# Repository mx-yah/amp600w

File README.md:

# High-efficiency 600W sound amplifier

A high-performance high-power class-D amplifier that enables true premium 
sound quality with high-efficiency class-D technology

Based on the TPA3255DDV integrated circuit from Texas Instruments.

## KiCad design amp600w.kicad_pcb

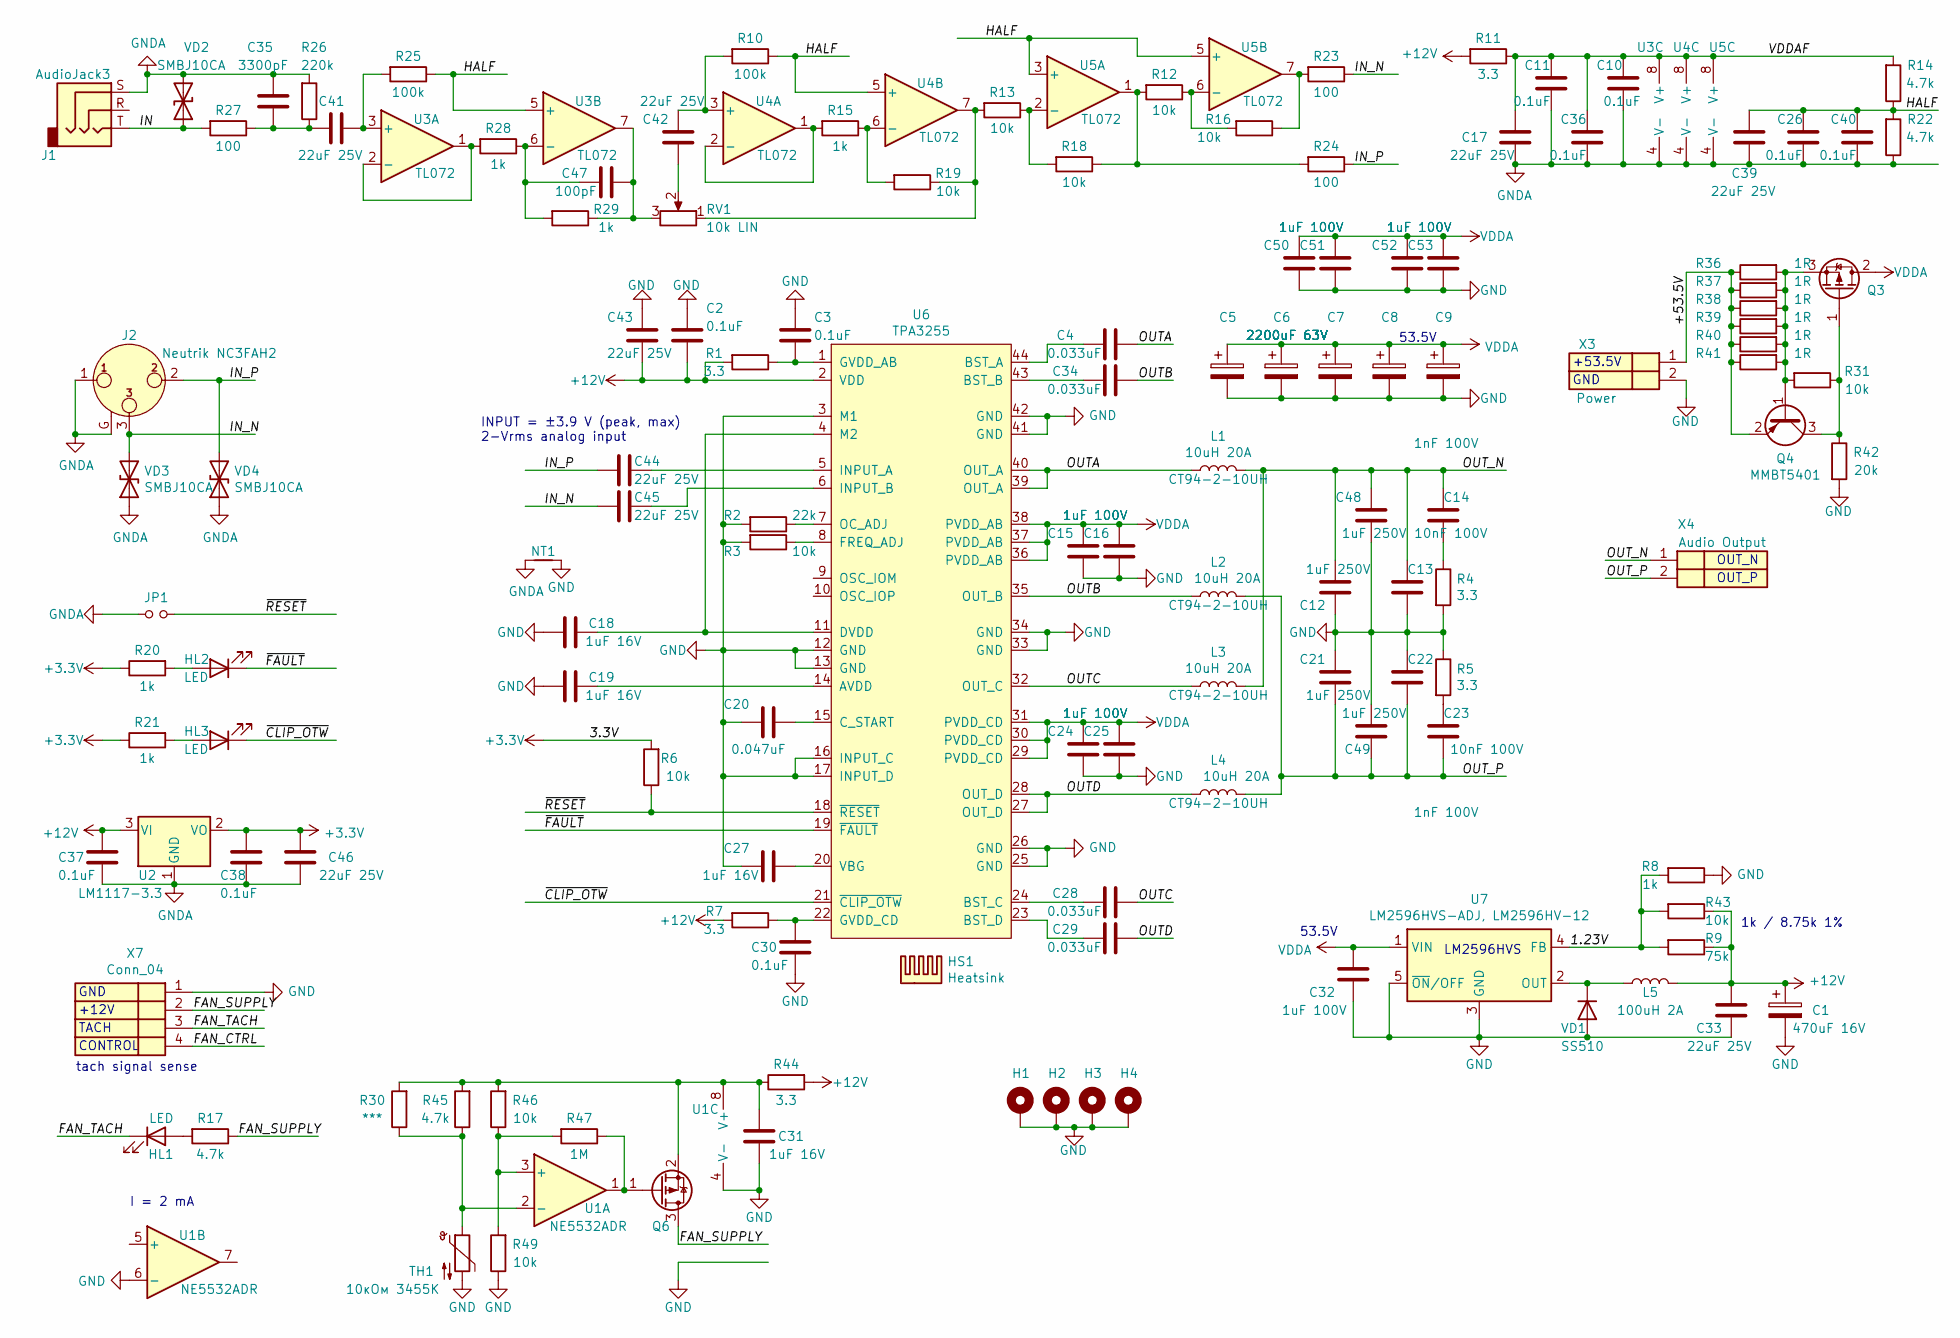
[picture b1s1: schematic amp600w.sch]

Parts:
C1: 470uF 16V; CP_Radial_D8.0mm_P3.50mm
C2, C3, C10, C11, C26, C30, C36, C37, C38, C40: 0.1uF; C_0603_1608Metric
C4, C28, C29, C34: 0.033uF; C_0603_1608Metric
C5, C6, C7, C8, C9: 2200uF 63V; CP_Radial_D18.0mm_P7.50mm
C12, C21, C48, C49: 1uF 250V; C_Rect_L18.0mm_W9.0mm_P15.00mm_FKS3_FKP3
C13, C22: 1nF 100V; C_1206_3216Metric
C14, C23: 10nF 100V; C_0805_2012Metric
C15, C16, C24, C25, C32, C50, C51, C52, C53: 1uF 100V; C_1210_3225Metric
C17, C33, C39, C41, C42, C43, C44, C45, C46: 22uF 25V; C_1210_3225Metric
C18, C19, C27, C31: 1uF 16V; C_0603_1608Metric
C20: 0.047uF; C_0603_1608Metric
C35: 3300pF; C_0603_1608Metric
C47: 100pF; C_0603_1608Metric
H1, H2, H3, H4: MountingHole_Pad; MountingHole_3.5mm_Pad_Via
HL1: LED; LED_D3.0mm
HL2, HL3: LED; LED_D3.0mm_Horizontal_O6.35mm_Z6.0mm
HS1: Heatsink; HEATSINK_LGA1156
J1: AudioJack3; Jack_3.5mm_Switronic_ST-005-G_horizontal
J2: XLR3_Ground; Jack_XLR_Neutrik_NC3FAH2_Horizontal
JP1: Jumper_NO_Small; PinHeader_1x02_P2.54mm_Vertical
L1, L2, L3, L4: 10uH 20A; L_Toroid_Vertical_L33.0mm_W17.8mm_P12.70mm_Pulse_KM-5
L5: 100uH 2A; L_12x12mm_H8mm
NT1: Net-Tie_2; NetTie-2_SMD_Pad0.5mm
Q3: IRF9540NSTRLPBF; TO-263-2
Q4: MMBT5401; SOT-23
Q6: IRLML9303; SOT-23
R1, R4, R5, R7, R11, R44: 3.3; R_1206_3216Metric
R2: 22k; R_0603_1608Metric
R3, R6, R12, R13, R16, R18, R19, R31, R43, R46, R49: 10k; R_0603_1608Metric
R8, R15, R20, R21, R28, R29: 1k; R_0603_1608Metric
R9: 75k; R_0603_1608Metric
R10, R25: 100k; R_0603_1608Metric
R14, R17, R22, R45: 4.7k; R_0603_1608Metric
R23, R24, R27: 100; R_0603_1608Metric
R26: 220k; R_0603_1608Metric
R30: ***; R_0603_1608Metric
R36, R37, R38, R39, R40, R41: 1R; R_1812_4532Metric
R42: 20k; R_0805_2012Metric
R47: 1M; R_0603_1608Metric
RV1: 10k LIN; Potentiometer_Piher_T-16H_Single_Horizontal
TH1: 10кОм 3455K; R_0603_1608Metric
U1: NE5532ADR; SO-8_3.9x4.9mm_P1.27mm
U2: LM1117-3.3; SOT-223-3_TabPin2
U3, U4, U5: TL072; SO-8_3.9x4.9mm_P1.27mm
U6: TPA3255; TPA3255DDV
U7: LM2596HVS-ADJ, LM2596HV-12; TO-263-5_TabPin3
VD1: SS510; D_SMC
VD2, VD3, VD4: SMBJ10CA; D_SMB
X3: Power; TerminalBlock_Degson_DG25C-B_P7.62mm
X4: Audio Output; TerminalBlock_Degson_DG25C-B_P7.62mm
X7: Conn_04; FanPinHeader_1x04_P2.54mm_Vertical

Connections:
+3V3: C38.2, C46.1, R6.2, R20.1, R21.1, U2.2 (VO)
+12V: C1.1, C2.2, C33.2, C37.2, C43.2, L5.2, R1.2, R7.2, R9.1, R11.2, R43.1, R44.2, U2.3 (VI), U6.2 (VDD)
/1.23V: R8.2, R9.2, R43.2, U7.4 (FB)
/+53.5V: Q4.2 (E), R36.1, R37.1, R38.1, R39.1, R40.1, R41.1, X3.1
/FAN_SUPPLY: Q6.3 (D), R17.1, X7.2
/FAN_TACH: HL1.1 (K), X7.3
/HALF: C26.2, C39.1, C40.1, R10.1, R14.1, R22.2, R25.1, U3.5 (+), U4.5 (+), U5.3 (+), U5.5 (+)
/IN: J1.T, R27.2, VD2.1 (A1)
/IN_N: C45.2, J2.3, R23.1, VD3.2 (A2)
/IN_P: C44.2, J2.2, R24.1, VD4.2 (A2)
/OUTA: C4.1, L1.1, U6.39 (OUT_A), U6.40 (OUT_A)
/OUTB: C34.1, L2.1, U6.35 (OUT_B)
/OUTC: C28.1, L3.1, U6.32 (OUT_C)
/OUTD: C29.1, L4.1, U6.27 (OUT_D), U6.28 (OUT_D)
/OUT_N: C12.2, C13.2, C14.2, C48.2, L1.2, L3.2, X4.1
/OUT_P: C21.1, C22.1, C23.1, C49.1, L2.2, L4.2, X4.2
/VDDAF: C10.1, C11.1, C17.1, C36.1, R11.1, R14.2, U3.8 (V+), U4.8 (V+), U5.8 (V+)
/~CLIP_OTW: HL3.1 (K), U6.21 (~CLIP_OTW)
/~FAULT: HL2.1 (K), U6.19 (~FAULT)
/~RESET: JP1.2, R6.1, U6.18 (~RESET)
GND: C1.2, C2.1, C3.1, C5.2, C6.2, C7.2, C8.2, C9.2, C12.1, C13.1, C15.1, C16.1, C18.1, C19.1, C20.1, C21.2, C22.2, C24.1, C25.1, C27.1, C30.1, C31.1, C32.1, C33.1, C43.1, C48.1, C49.2, C50.1, C51.1, C52.1, C53.1, H1.1, H2.1, H3.1, H4.1, NT1.2, R2.2, R3.2, R4.2, R5.1, R8.1, R42.2, R49.1, TH1.2, U1.4 (V-), U1.6 (-), U6.3 (M1), U6.12 (GND), U6.13 (GND), U6.16 (INPUT_C), U6.17 (INPUT_D), U6.25 (GND), U6.26 (GND), U6.33 (GND), U6.34 (GND), U6.41 (GND), U6.42 (GND), U7.3 (GND), U7.5 (~ON~/OFF), VD1.2 (A), X3.2, X7.1
GNDA: C10.2, C11.2, C17.2, C26.1, C35.1, C36.2, C37.1, C38.1, C39.2, C40.2, C46.2, J1.S, J2.1, J2.G, JP1.1, NT1.1, R22.1, R26.2, U2.1 (GND), U3.4 (V-), U4.4 (V-), U5.4 (V-), VD2.2 (A2), VD3.1 (A1), VD4.1 (A1)
unnamed: C3.2, R1.1, U6.1 (GVDD_AB)
unnamed: C4.2, U6.44 (BST_A)
unnamed: C14.1, R4.1
unnamed: C18.2, U6.4 (M2), U6.11 (DVDD)
unnamed: C19.2, U6.14 (AVDD)
unnamed: C20.2, U6.15 (C_START)
unnamed: C23.2, R5.2
unnamed: C27.2, U6.20 (VBG)
unnamed: C28.2, U6.24 (BST_C)
unnamed: C29.2, U6.23 (BST_D)
unnamed: C30.2, R7.1, U6.22 (GVDD_CD)
unnamed: C31.2, Q6.2 (S), R30.2, R44.1, R45.2, R46.2, U1.8 (V+)
unnamed: C34.2, U6.43 (BST_B)
unnamed: C35.2, C41.2, R26.1, R27.1
unnamed: C41.1, R25.2, U3.3 (+)
unnamed: C42.1, RV1.2
unnamed: C42.2, R10.2, U4.3 (+)
unnamed: C44.1, U6.5 (INPUT_A)
unnamed: C45.1, U6.6 (INPUT_B)
unnamed: C47.1, R28.1, R29.2, U3.6 (-)
unnamed: C47.2, R29.1, RV1.3, U3.7
unnamed: HL1.2 (A), R17.2
unnamed: HL2.2 (A), R20.2
unnamed: HL3.2 (A), R21.2
unnamed: L5.1, U7.2 (OUT), VD1.1 (K)
unnamed: Q3.1 (G), Q4.3 (C), R31.1, R42.1
unnamed: Q3.3 (S), Q4.1 (B), R31.2, R36.2, R37.2, R38.2, R39.2, R40.2, R41.2
unnamed: Q6.1 (G), R47.1, U1.1
unnamed: R2.1, U6.7 (OC_ADJ)
unnamed: R3.1, U6.8 (FREQ_ADJ)
unnamed: R12.1, R16.2, U5.6 (-)
unnamed: R12.2, R18.1, R24.2, U5.1
unnamed: R13.1, R18.2, U5.2 (-)
unnamed: R13.2, R19.1, RV1.1, U4.7
unnamed: R15.1, R19.2, U4.6 (-)
unnamed: R15.2, U4.1, U4.2 (-)
unnamed: R16.1, R23.2, U5.7
unnamed: R28.2, U3.1, U3.2 (-)
unnamed: R30.1, R45.1, TH1.1, U1.2 (-)
unnamed: R46.1, R47.2, R49.2, U1.3 (+)
VDDA: C5.1, C6.1, C7.1, C8.1, C9.1, C15.2, C16.2, C24.2, C25.2, C32.2, C50.2, C51.2, C52.2, C53.2, Q3.2 (D), U6.29 (PVDD_CD), U6.30 (PVDD_CD), U6.31 (PVDD_CD), U6.36 (PVDD_AB), U6.37 (PVDD_AB), U6.38 (PVDD_AB), U7.1 (VIN)

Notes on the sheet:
INPUT = ±3.9 V (peak, max) 2-Vrms analog input
LM2596HVS
1k / 8.75k 1%
GND
+12V
TACH
CONTROL
tach signal sense
53.5V
+53.5V
OUT_N
OUT_P
I = 2 mA

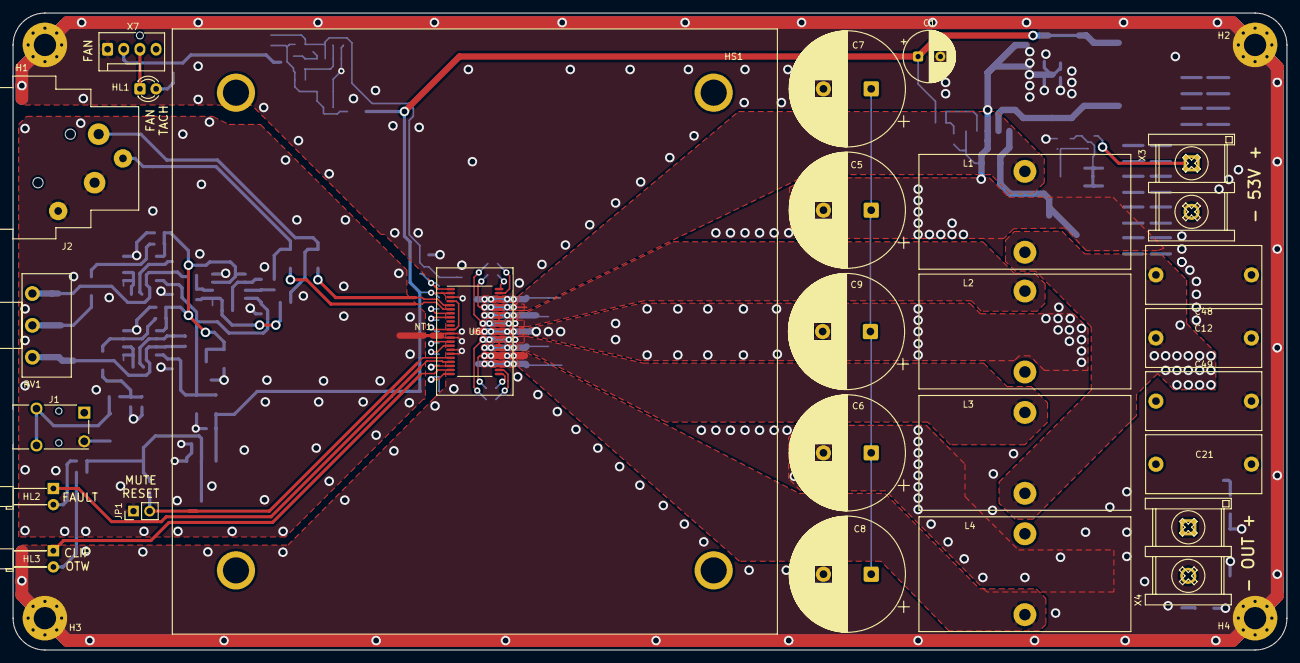
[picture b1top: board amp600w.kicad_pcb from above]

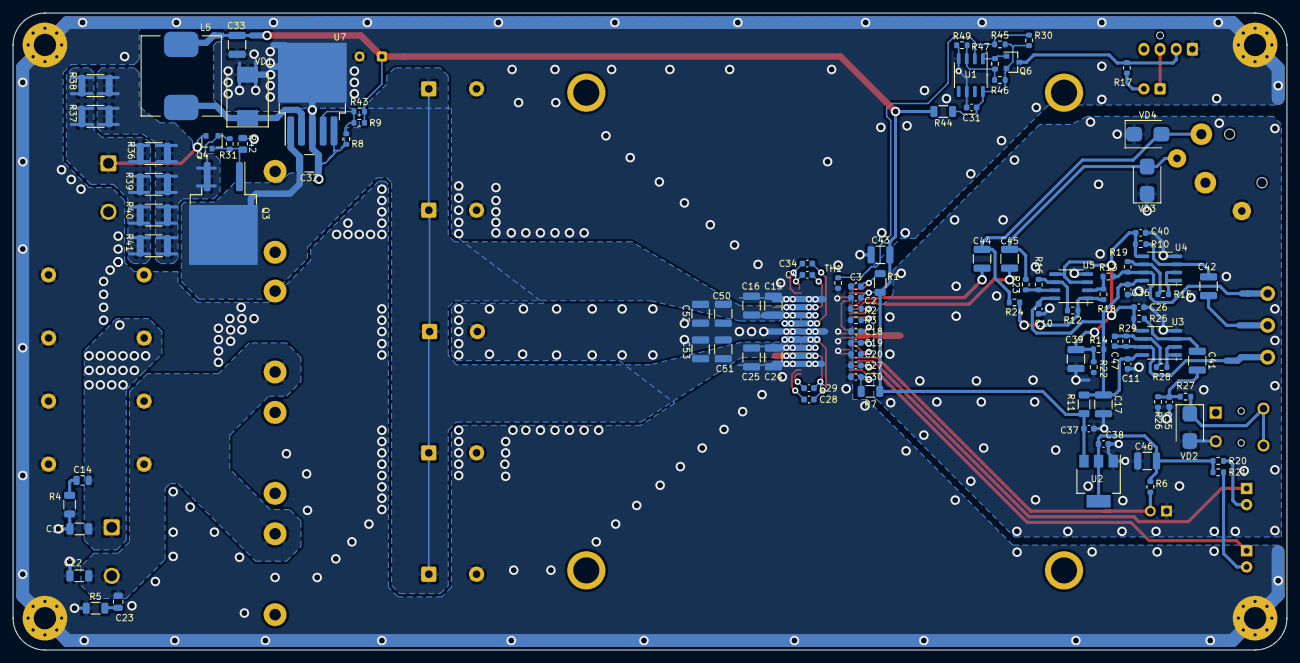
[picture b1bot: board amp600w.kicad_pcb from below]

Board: 2 copper layers, 200.0 x 100.0 mm, 133 parts (102 on the bottom side), 63 nets.

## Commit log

2020-11-25 init
2020-11-28 add fan control
2020-12-03 some eddit
2020-12-07 differencial input
2020-12-07 analog input
2020-12-09 two fan controll, two charge controll
2020-12-11 board init
2020-12-14 board
2020-12-14 images
2020-12-15 output files
2020-12-16 add capacitor
2020-12-16 add capacitor2
2020-12-18 LTspice
2021-02-13 add R31 10k 0603
2021-02-13 add simulation pictures
2021-04-06 new 3d model of the coil

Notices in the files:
parts and their libraries:
Copyright 2016 Accelerated Designs. All rights reserved.
